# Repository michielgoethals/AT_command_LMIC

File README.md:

# AT-Commands RN2483 using LMIC

This repository is a expansion of the LMIC library to work with the RN2483 AT commands.

An overview of which commands are currently implemented and working correctly can be found in the DOC folder as a PDF.

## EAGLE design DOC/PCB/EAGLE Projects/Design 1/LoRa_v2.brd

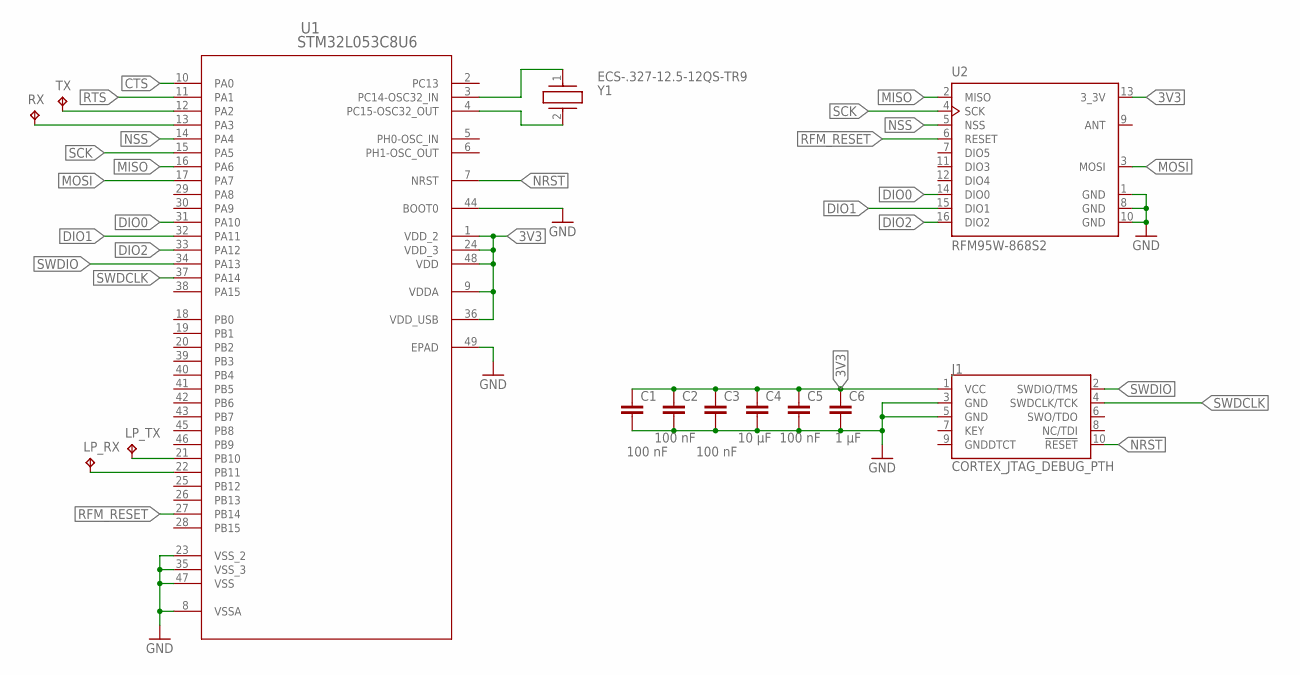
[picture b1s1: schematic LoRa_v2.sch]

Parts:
C1, C2, C3, C5: 100 nF; C0402
C4: 10 µF; C0402
C6: 1 µF; C0402
J1: CORTEX_JTAG_DEBUG_PTH; 2X5-PTH-1.27MM
LP_RX: TPB1,27; B1,27
LP_TX: TPB1,27; B1,27
RX: TPB1,27; B1,27
TX: TPB1,27; B1,27
U1: STM32L053C8U6; UFQFPN-48_STM
U2: RFM95W-868S2; XCVR_RFM95W-868S2
Y1: ECS-.327-12.5-12QS-TR9; ECS32712512QSTR9

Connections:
3V3: C1.1, C2.1, C3.1, C4.1, C5.1, C6.1, J1.1 (VCC), U1.1 (VDD_2), U1.9 (VDDA), U1.24 (VDD_3), U1.36 (VDD_USB), U1.48 (VDD), U2.13 (3_3V)
CTS: U1.10 (PA0)
DIO0: U1.31 (PA10), U2.14 (DIO0)
DIO1: U1.32 (PA11), U2.15 (DIO1)
DIO2: U1.33 (PA12), U2.16 (DIO2)
GND: C1.2, C2.2, C3.2, C4.2, C5.2, C6.2, J1.3 (GND), J1.5 (GND), U1.8 (VSSA), U1.23 (VSS_2), U1.35 (VSS_3), U1.44 (BOOT0), U1.47 (VSS), U1.49 (EPAD), U2.1 (GND), U2.8 (GND), U2.10 (GND)
MISO: U1.16 (PA6), U2.2 (MISO)
MOSI: U1.17 (PA7), U2.3 (MOSI)
unnamed: U1.3 (PC14-OSC32_IN), Y1.1
unnamed: LP_RX.TP, U1.22 (PB11)
unnamed: U1.4 (PC15-OSC32_OUT), Y1.2
unnamed: LP_TX.TP, U1.21 (PB10)
NRST: J1.10 (!RESET), U1.7 (NRST)
NSS: U1.14 (PA4), U2.5 (NSS)
RFM_RESET: U1.27 (PB14), U2.6 (RESET)
RTS: U1.11 (PA1)
RX: RX.TP, U1.13 (PA3)
SCK: U1.15 (PA5), U2.4 (SCK)
SWDCLK: J1.4 (SWDCLK/TCK), U1.37 (PA14)
SWDIO: J1.2 (SWDIO/TMS), U1.34 (PA13)
TX: TX.TP, U1.12 (PA2)

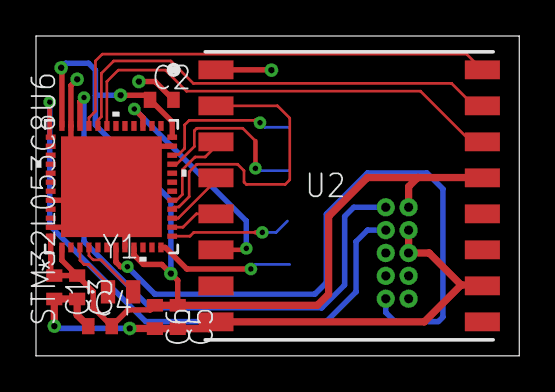
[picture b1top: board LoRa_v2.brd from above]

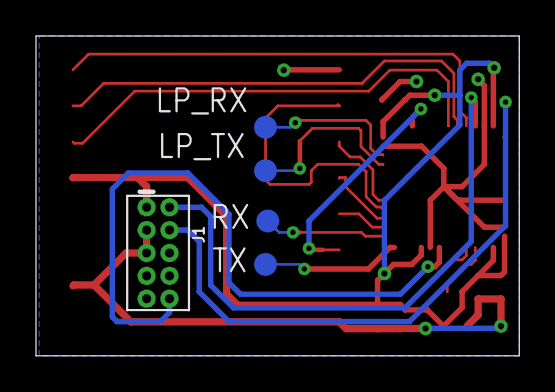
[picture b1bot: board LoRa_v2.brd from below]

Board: 2 copper layers, 26.8 x 17.8 mm, 14 parts (5 on the bottom side), 19 nets.

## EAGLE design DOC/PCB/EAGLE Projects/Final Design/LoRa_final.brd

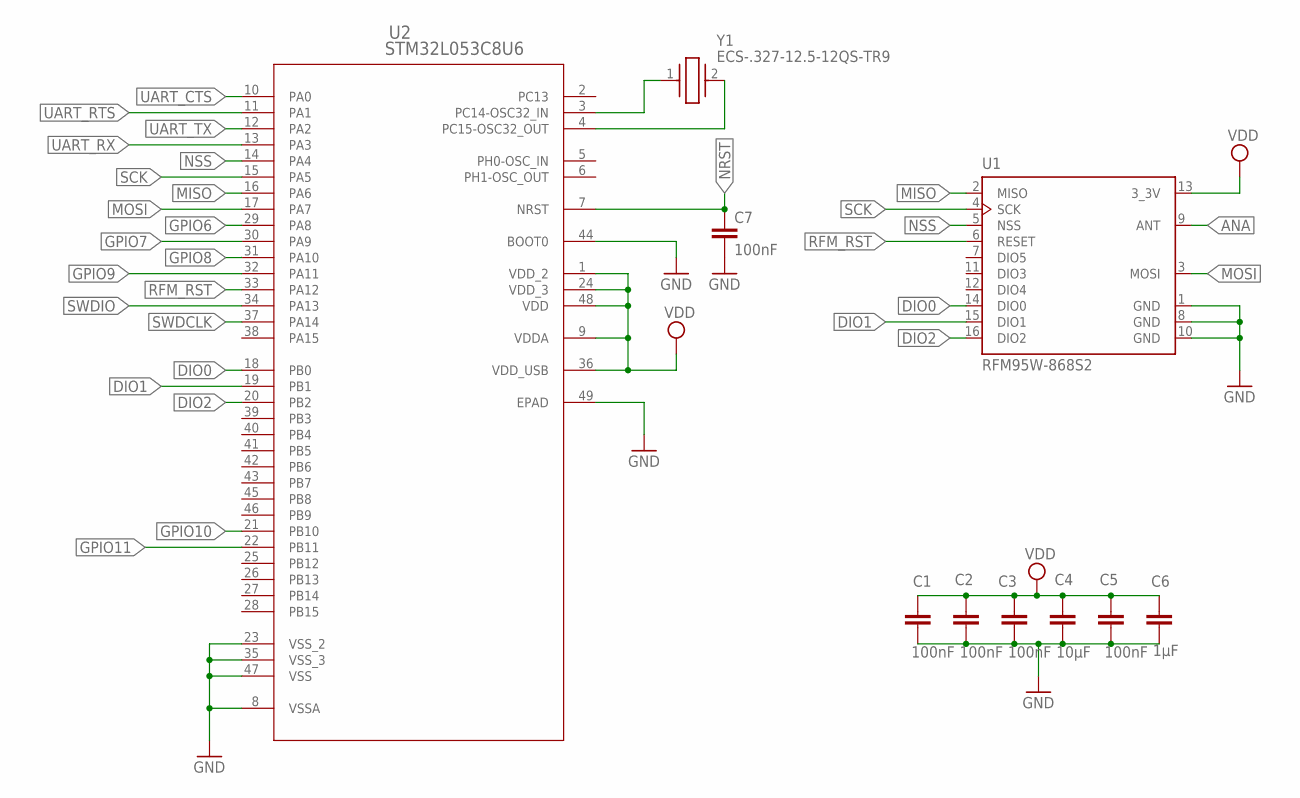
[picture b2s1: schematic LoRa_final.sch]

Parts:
C1, C2, C3, C5, C7: 100nF; C0402K
C4: 10µF; C0402K
C6: 1µF; C0402K
U1: RFM95W-868S2; XCVR_RFM95W-868S2
U2: STM32L053C8U6; UFQFPN-48_STM
Y1: ECS-.327-12.5-12QS-TR9; ECS32712512QSTR9

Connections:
ANA: U1.9 (ANT)
DIO0: U1.14 (DIO0), U2.18 (PB0)
DIO1: U1.15 (DIO1), U2.19 (PB1)
DIO2: U1.16 (DIO2), U2.20 (PB2)
GND: C1.2, C2.2, C3.2, C4.2, C5.2, C6.2, C7.2, U1.1 (GND), U1.8 (GND), U1.10 (GND), U2.8 (VSSA), U2.23 (VSS_2), U2.35 (VSS_3), U2.44 (BOOT0), U2.47 (VSS), U2.49 (EPAD)
GPIO6: U2.29 (PA8)
GPIO7: U2.30 (PA9)
GPIO8: U2.31 (PA10)
GPIO9: U2.32 (PA11)
GPIO10: U2.21 (PB10)
GPIO11: U2.22 (PB11)
MISO: U1.2 (MISO), U2.16 (PA6)
MOSI: U1.3 (MOSI), U2.17 (PA7)
unnamed: U2.3 (PC14-OSC32_IN), Y1.1
unnamed: U2.4 (PC15-OSC32_OUT), Y1.2
NRST: C7.1, U2.7 (NRST)
NSS: U1.5 (NSS), U2.14 (PA4)
RFM_RST: U1.6 (RESET), U2.33 (PA12)
SCK: U1.4 (SCK), U2.15 (PA5)
SWDCLK: U2.37 (PA14)
SWDIO: U2.34 (PA13)
UART_CTS: U2.10 (PA0)
UART_RTS: U2.11 (PA1)
UART_RX: U2.13 (PA3)
UART_TX: U2.12 (PA2)
VDD: C1.1, C2.1, C3.1, C4.1, C5.1, C6.1, U1.13 (3_3V), U2.1 (VDD_2), U2.9 (VDDA), U2.24 (VDD_3), U2.36 (VDD_USB), U2.48 (VDD)

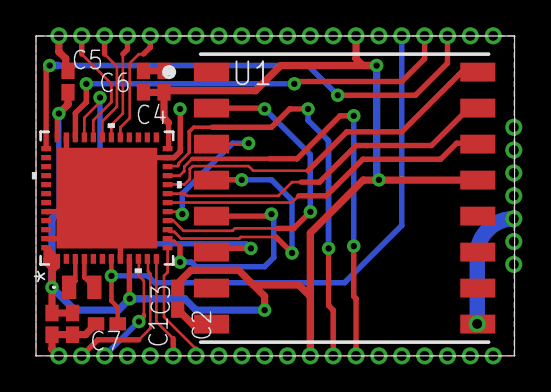
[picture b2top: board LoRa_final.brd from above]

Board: 2 copper layers, 26.6 x 17.8 mm, 10 parts (0 on the bottom side), 13 nets.

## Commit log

2022-11-22 created correct folder structure
2022-11-22 removed some folders
2022-11-22 fixed files
2022-11-22 removed file
2022-11-22 added changes
2022-11-29 class to read uart commandos
2022-11-29 added parse functions
2022-11-29 renamed files
2022-12-04 added functionality
2022-12-05 extended wrapper and commands
2022-12-07 finished reset, set commands
2022-12-07 typo
2022-12-09 added all mac commands
2022-12-11 added functions definitions
2022-12-13 added all mac set, join, tx commands
2022-12-13 added return to functions to remove warnings when compiling
2022-12-14 fixed return of char*
2022-12-14 added communication between the 2 classes
2022-12-19 updated to LMIC dependancy
2022-12-19 added otaa joining
2022-12-19 added support for uppercase commands
2022-12-20 expanded wrapper
2022-12-21 joining and sending packets works
2022-12-21 fixed typo
2022-12-21 still bug when returing deveui
2023-02-21 joining and sending packets works v2
2023-02-21 update working joining otaa
2023-02-21 added implementation for abp joining
2023-02-21 added implementation for abp joining not working yet
2023-02-23 tested some code for abp joining, not working yet
2023-02-24 added status register functionality
2023-02-24 added status register functionality and test
2023-02-24 added set channel functionality not tested yet
2023-02-24 added EEPROM saving of all parameters
2023-02-24 get receive window 2 parameters added
2023-02-25 cleaned up some code and testing
2023-02-25 added default values of return parameters
2023-02-25 renamed file
2023-02-25 renamed function names
2023-02-25 added mac get channel functionality
2023-02-28 removed softwareSerial and use on board uart
2023-03-01 renamed mac function names and addes sys reset
2023-03-01 added return values for basic functions
2023-03-02 expanded return strings of mac commands
2023-03-02 fixed returned devaddr when joining
2023-03-07 fixed some return values and bugs
2023-03-07 eeprom save channels bug
2023-03-09 added comment
2023-03-09 edit tx method
2023-03-21 fixed tx function and reset now unjoins communication
2023-03-21 added description
2023-03-30 added abp functionality and return types
2023-03-30 renamed files and typo
2023-03-30 small implementation of sys reset
2023-03-30 fixed keys restore with sys reset command
2023-03-30 changed function names
2023-03-30 added radio wrap files
2023-03-30 added all radio functions
2023-03-30 fixed include
2023-03-31 tested sys reset and abp and otaa
2023-04-24 changed responses back to host mcu
2023-04-24 renamed
2023-04-24 added functions to cpp
2023-04-24 added some comments
2023-04-24 removed responses from non working functions
2023-04-24 added class variable
2023-04-24 added all sys functions to class
2023-04-24 added possible responses array
2023-04-26 added callbacks to main
2023-04-26 moved os_init to main
2023-04-26 changed implementation to read buffer
2023-04-26 optimized delay so it is faster
2023-04-26 fixed length check of keys and euis
2023-04-27 added internal HSI implementation
2023-04-27 added posible auto baud rate implentation
2023-04-27 code cleanup
2023-04-27 fixed wrong use variable
2023-04-27 pinmapping
2023-04-27 removed huart stm
2023-04-27 added clocks to gpio
2023-04-27 added return type to all functions
2023-04-27 removed sys command defenition
2023-04-27 added blink to check if gpios working
2023-04-27 typos
2023-04-27 Fixed multiple the same responses
2023-04-27 removed attribute
2023-04-27 fixed bugs
2023-04-27 adde implementation
2023-04-28 added frame counters setters an getters
2023-04-28 added comments to functions, frame counters
2023-04-28 implemented sys commands
2023-04-28 removed set pinmode, get pindig and pinana func
2023-04-28 removed blink from main
2023-04-28 added comments
2023-04-28 fixed startup message and some typos
2023-04-28 added restore configuration and call @ startup
2023-04-28 fixed implementation of reset function
2023-04-30 added function fot better overview
2023-04-30 added working factory reset
2023-04-30 changed pins
2023-04-30 implementation of most radio (set) commands
2023-05-01 added pause and resume functionality
2023-05-01 added implementation for all radio set commands
2023-05-01 removed gpio port c clock
2023-05-01 added parse commands for all radio commands
2023-05-01 changed return parameters get commands
2023-05-01 added radio get command implementation
2023-05-01 edit readme
2023-05-02 removed blink job
2023-05-02 added code from radio.c lmic to set registers
2023-05-02 removed unncessary registers
2023-05-04 removed rtc
2023-05-04 few changes to default parameters
2023-05-04 removed hrtc
2023-05-06 few changes to radio layer
2023-05-09 added command ref this code is based on
2023-05-14 added HAL UART instead of serial of arduino
2023-05-14 added uart and rtc init functions
2023-05-14 added RTC initalisation and wake up
2023-05-14 sleep and wake up implementation
2023-05-14 back to serial
2023-05-14 cleanup (working rtc)
2023-05-14 added working uart stm hal
2023-05-14 added platformIO conf file
2023-05-14 change
2023-05-14 added uart handler to mac wrapper
2023-05-15 added error handler to timer setup
2023-05-15 changed comment
2023-05-15 added event callbacks
2023-05-15 added cleaner implementation
2023-05-15 deactivate RTC timer when finished sleeping
2023-05-16 Working sys sleep for longer times
2023-05-16 Removed char warning when setting default keys
2023-05-16 fixed joining and tx working (not cnf)
2023-05-16 removed unused clock gpio C
2023-05-18 Moved used command ref to DOC
2023-05-18 Added PCB files
2023-05-18 Added all pdf's
2023-05-19 fixed saving channel information
2023-05-20 changed lib readme implementation
2023-05-20 adde memory map to readme
2023-05-20 added message received callback
2023-05-20 fixed send byte array is same as at param
2023-05-23 changed clock to 4 MHz also uart HSI
2023-05-23 added support for used gpio
2023-05-23 changed docs
2023-05-23 fixed bytes send
2023-05-23 fixed send data to add 0 in front
2023-05-23 regulator to scale 3
2023-05-24 fixed bug setting afc and rx bandwith
2023-05-30 Added Supported AT-commands file

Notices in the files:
parts and their libraries:
SparkFun-Connectors: Licensing: Creative Commons ShareAlike 4.0 International - https://creativecommons.org/licenses/by-sa/4.0
COPYRIGHT: Copyright (C) 2023 Ultra Librarian. All rights reserved.
